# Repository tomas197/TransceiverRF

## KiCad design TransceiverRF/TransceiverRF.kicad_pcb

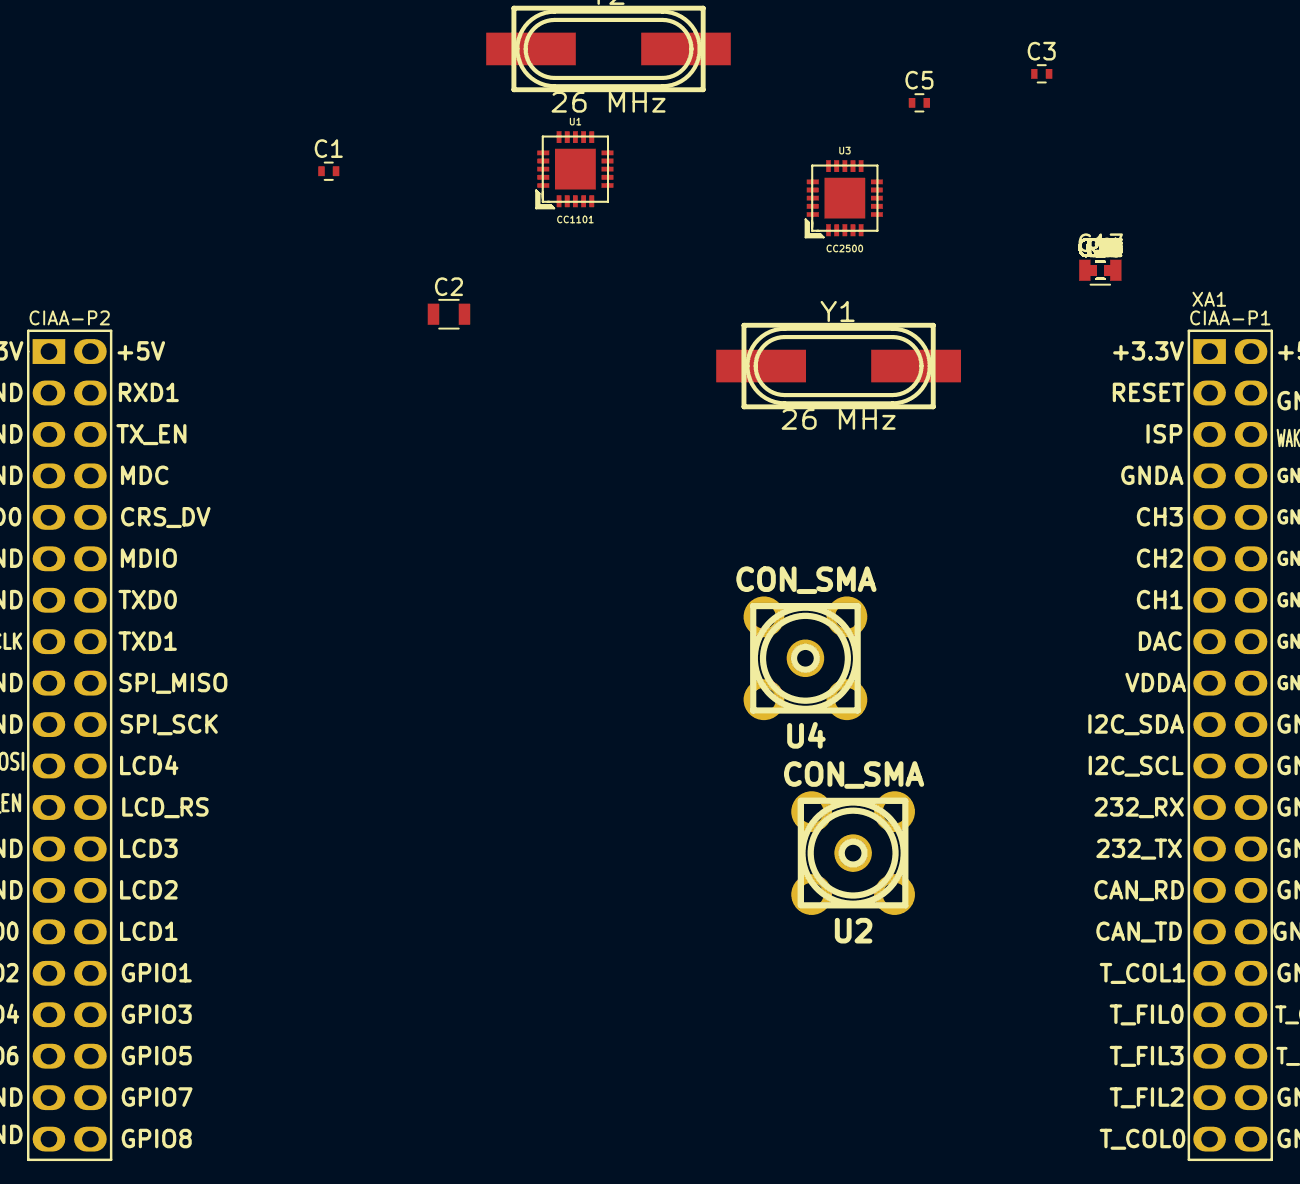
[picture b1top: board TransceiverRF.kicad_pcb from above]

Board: 2 copper layers, 48 parts (0 on the bottom side), 36 nets, no tracks yet.

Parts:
C1, C6, C13, C18: 220pF; R_0402
C2, C17: 1uF; R_0805
C3, C4, C10, C11, C12, C14, C19, C20, C26, C28, C29, C30: 100nF; R_0402
C5, C7: 3,9pF; R_0402
C8: 8,2pF; R_0402
C9: 5,6pF; R_0402
C15, C16, C31, C32: 27pF; R_0402
C21, C23: 100pF; R_0402
C22, C27: 1pF; R_0402
C24: 1,8pF; R_0402
C25: 1,5pF; R_0402
L1, L3, L4: 27nH; R_0402
L2: 22nH; R_0402
L5, L6, L7: 1,2nH; R_0402
R1, R2: 56K; R_0402
U1: CC1101; qfn-20
U2, U4: CON_SMA; sma_straight_32k101-400l5
U3: CC2500; qfn-20
XA1: Conn_Poncho2P_2x_20x2; Conn_Poncho_Mediano
Y1, Y2: 26 MHz; hc-49_smd

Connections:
+3V3: C1.1, C2.1, C3.1, C4.1, C10.1, C12.1, C14.1, C17.1, C18.1, C19.1, C20.1, C26.1, C29.1, C30.1, U1.4, U1.9, U1.11, U1.14, U1.15, U1.18, U3.4, U3.9, U3.11, U3.14, U3.15, U3.18, XA1.1, XA1.41
/CC1101/CSn_CC1101: U1.7, XA1.76
/CC1101/GDO1(opcional)_CC1101: U1.6, XA1.74
/CC1101/SI_CC1101: U1.20, XA1.46
/CC1101/SO_CC1101: U1.2, XA1.44
/CC2500/CSn_CC2500: U3.7, XA1.73
/CC2500/GDO1(opcional)_CC2500: U3.6, XA1.69
/CC2500/GDO2(opcional)_CC2500: U3.3, XA1.71
/CC2500/SI_CC2500: U3.20, XA1.61
/CC2500/SO_CC2500: U3.2, XA1.58
/Conectores/GDO1(opcional)_CC1101: U1.3, XA1.72
/Conectores/SCLK_1101: U1.1, XA1.55
/Conectores/SCLK_2500: U3.1, XA1.60
unnamed: C5.2, L1.2, U1.13
unnamed: C6.1, C9.1, L3.1
unnamed: C6.2, U2.1
unnamed: C7.1, L4.1, U1.12
unnamed: C7.2, L1.1, L2.2
unnamed: C8.1, L2.1, L3.2
unnamed: C11.1, U1.5
unnamed: C13.1, L4.2
unnamed: C15.1, U1.8, Y1.1
unnamed: C16.1, U1.10, Y1.2
unnamed: C21.1, U3.13
unnamed: C21.2, C22.1, L5.2
unnamed: C22.2, C24.1, L6.2, L7.1
unnamed: C23.1, U3.12
unnamed: C23.2, C27.1, L7.2
unnamed: C25.1, L6.1, U4.1
unnamed: C28.1, U3.5
unnamed: C31.1, U3.8, Y2.1
unnamed: C32.1, U3.10, Y2.2
unnamed: R1.2, U1.17
unnamed: R2.2, U3.17
unnamed: XA1.4, XA1.20, XA1.22, XA1.24, XA1.26, XA1.28, XA1.30, XA1.32, XA1.38, XA1.40
unnamed: XA1.43, XA1.45, XA1.47, XA1.51, XA1.53, XA1.57, XA1.59, XA1.65, XA1.67, XA1.77, XA1.79

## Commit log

2017-10-28 guardo los cambios
2017-11-13 agrego pcb
